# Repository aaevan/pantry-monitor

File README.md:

# pantry-monitor
Track the amounts of different staples using a raspi, a usb scale and large satisfying buttons.

See https://www.youtube.com/watch?v=ahMDome1ZE8 for a demo.

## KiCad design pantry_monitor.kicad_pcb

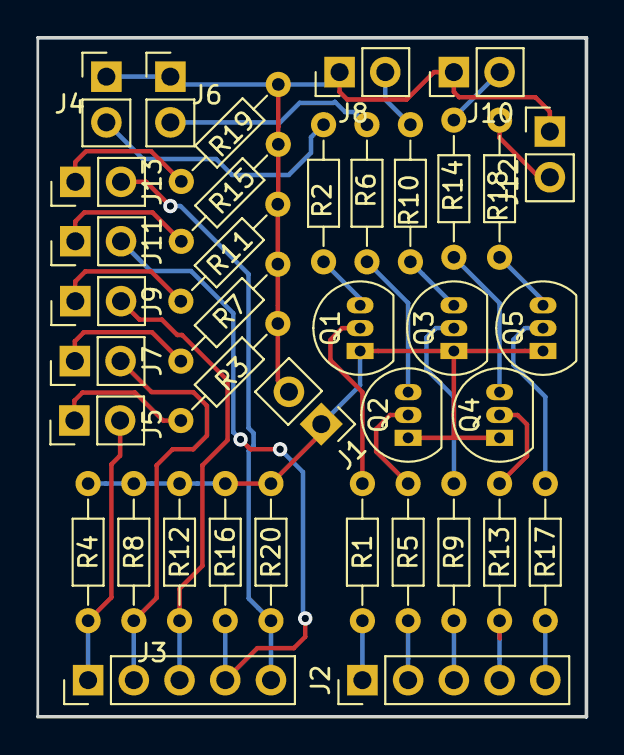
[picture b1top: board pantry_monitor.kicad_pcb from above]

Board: 2 copper layers, 30.5 x 37.7 mm, 38 parts (0 on the bottom side), 32 nets.

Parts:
J1: raspi vcc/gnd; Pin_Header_Straight_1x02_Pitch2.54mm
J2: LED input; Pin_Header_Straight_1x05_Pitch2.54mm
J3: Switch output; Pin_Header_Straight_1x05_Pitch2.54mm
J4: LED 1; Pin_Header_Straight_1x02_Pitch2.54mm
J5: Switch 1; Pin_Header_Straight_1x02_Pitch2.54mm
J6: LED 2; Pin_Header_Straight_1x02_Pitch2.54mm
J7: Switch 2; Pin_Header_Straight_1x02_Pitch2.54mm
J8: LED 3; Pin_Header_Straight_1x02_Pitch2.54mm
J9: Switch 3; Pin_Header_Straight_1x02_Pitch2.54mm
J10: LED 4; Pin_Header_Straight_1x02_Pitch2.54mm
J11: Switch 4; Pin_Header_Straight_1x02_Pitch2.54mm
J12: LED 5; Pin_Header_Straight_1x02_Pitch2.54mm
J13: Switch 5; Pin_Header_Straight_1x02_Pitch2.54mm
Q1, Q2, Q3, Q4, Q5: 2N3904; TO-92_Inline_Narrow_Oval
R1, R4, R5, R8, R9, R12, R13, R16, R17, R20: 1k; R_Axial_DIN0204_L3.6mm_D1.6mm_P7.62mm_Horizontal
R2, R6, R10, R14, R18: 220; R_Axial_DIN0204_L3.6mm_D1.6mm_P7.62mm_Horizontal
R3, R7, R11, R15, R19: 330; R_Axial_DIN0204_L3.6mm_D1.6mm_P7.62mm_Horizontal

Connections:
GND: J1.1, Q1.1, Q2.1, Q3.1, Q4.1, Q5.1, R4.2, R8.2, R12.2, R16.2, R20.2
LED1: J2.1, R1.1
LED2: J2.2, R5.1
LED3: J2.3, R9.1
LED4: J2.4, R13.1
LED5: J2.5, R17.1
unnamed: J4.2, R2.1
unnamed: J5.1, R3.2
unnamed: J6.2, R6.1
unnamed: J7.1, R7.2
unnamed: J8.2, R10.1
unnamed: J9.1, R11.2
unnamed: J10.2, R14.1
unnamed: J11.1, R15.2
unnamed: J12.2, R18.1
unnamed: J13.1, R19.2
unnamed: Q1.2, R1.2
unnamed: Q1.3, R2.2
unnamed: Q2.2, R5.2
unnamed: Q2.3, R6.2
unnamed: Q3.2, R9.2
unnamed: Q3.3, R10.2
unnamed: Q4.2, R13.2
unnamed: Q4.3, R14.2
unnamed: Q5.2, R17.2
unnamed: Q5.3, R18.2
Switch1: J3.1, J5.2, R4.1
Switch2: J3.2, J7.2, R8.1
Switch3: J3.3, J9.2, R12.1
Switch4: J3.4, J11.2, R16.1
Switch5: J3.5, J13.2, R20.1
VCC: J1.2, J4.1, J6.1, J8.1, J10.1, J12.1, R3.1, R7.1, R11.1, R15.1, R19.1

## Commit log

2018-12-30 Started work on schematic for button and LED board.
2018-12-30 Initial commit.
2018-12-30 Added netlist and component associations.
2018-12-30 First mostly functional version of board.
2018-12-31 Generated gerbers, fixed transistor footprints.
2019-01-06 Added a tiny script as a test commit.:
2019-01-06 Moved around some files to clean up the root directory.
2019-01-06 Started mockup of behavior and made dummy functions.
2019-01-06 Added an image to README.md
2019-01-08 Tracks inputs properly.
2019-01-11 Added scale_test.py, an attempt to wrangle numbers out of raw byte values output from /dev/hidraw0.
2019-01-11 Cleaned up output of scale_test.
2019-01-12 Cleaned up and improved scale measurement. Added various utility functions.
2019-01-13 Integrated scale measurement and control into one file.
2019-01-13 Fixed up logic between buttons and scale. Framework is in place to measure staples.
2019-01-13 Added a few todo items.
2019-01-15 Started work on logging.
2019-01-15 Worked more on logging.
2019-01-15 Got logging working, barely.
2019-01-16 Backing up various changes.
2019-01-16 log file information now can be sent through a notify.run notification using notify_script.py
2019-01-17 Started work on finding time differences between lines of logfile.
2019-01-18 Reports correctly approximate number of days remaining of each staple.
2019-01-18 made minor change from main computer
2019-01-19 Worked on tallying usage over time in tally_usage_within_interval
2019-01-19 Started debugging on pi
2019-01-19 created legible_usage_stats
2019-01-19 implemented compare_stock_with_usage
2019-01-19 added notifcations to main script (gpio_control.py) and assumed python path.
2019-01-19 syncing with other computer
2019-01-19 Started compiling documentation piece
2019-01-19 Rough draft of documentation piece.
2019-01-19 Small changes to process.txt
2019-01-21 Cleaned up process.txt
2019-01-22 Changed a few pieces in the main documentation file.
2019-01-23 Further edits to process.txt
2019-01-24 A few more edits to process.txt
2019-01-25 small edit to process.txt
2019-02-01 continued work on check_point_within_arc
2019-02-18 Added documentation photos.
2019-02-18 Deleted unused photos.
2021-04-30 add link to youtube video demoing function
